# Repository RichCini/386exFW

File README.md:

# 386ex Firmware Prototyping/Design Board
386EX-target firmware design board based on the design from Ed Nisley and his Firmware Furnace column
in Circuit Cellar. The article series spanned Issues 31 to 65 (roughly 1993 to 1995). The hardware
design -- a short ISA card built on a Jameco prototyping card -- provided an easy way to interface
to the ISA bus and had memory (EEPROM/ROM/NVRAM). a timer, watchdog, LED and switch inputs, and two
types of LCD displays. 

The first part of the series (Issues 31- 46) dealt with the hardware design, while later articles
discussed something Ed called the "Firmware Furnace Task Switcher", a functional protected-mode
software platform. The software discussion began in Issue 48 and ended with Issue 65. Issue 65
seems to point to future columns on the topic, but they never seemed to appear.

## Status
The schematics have been converted and the board plotted. It has not been built yet. Of the
design elements, the only feature I didn't redraw was the bitmapped graphics LCD panel, the
discission of which began in Issue 42. Options were the Optrex (Kyocera) DMF651 640x200 or the 
Matsushita EDM-LG64AA44D 640x400 panel.

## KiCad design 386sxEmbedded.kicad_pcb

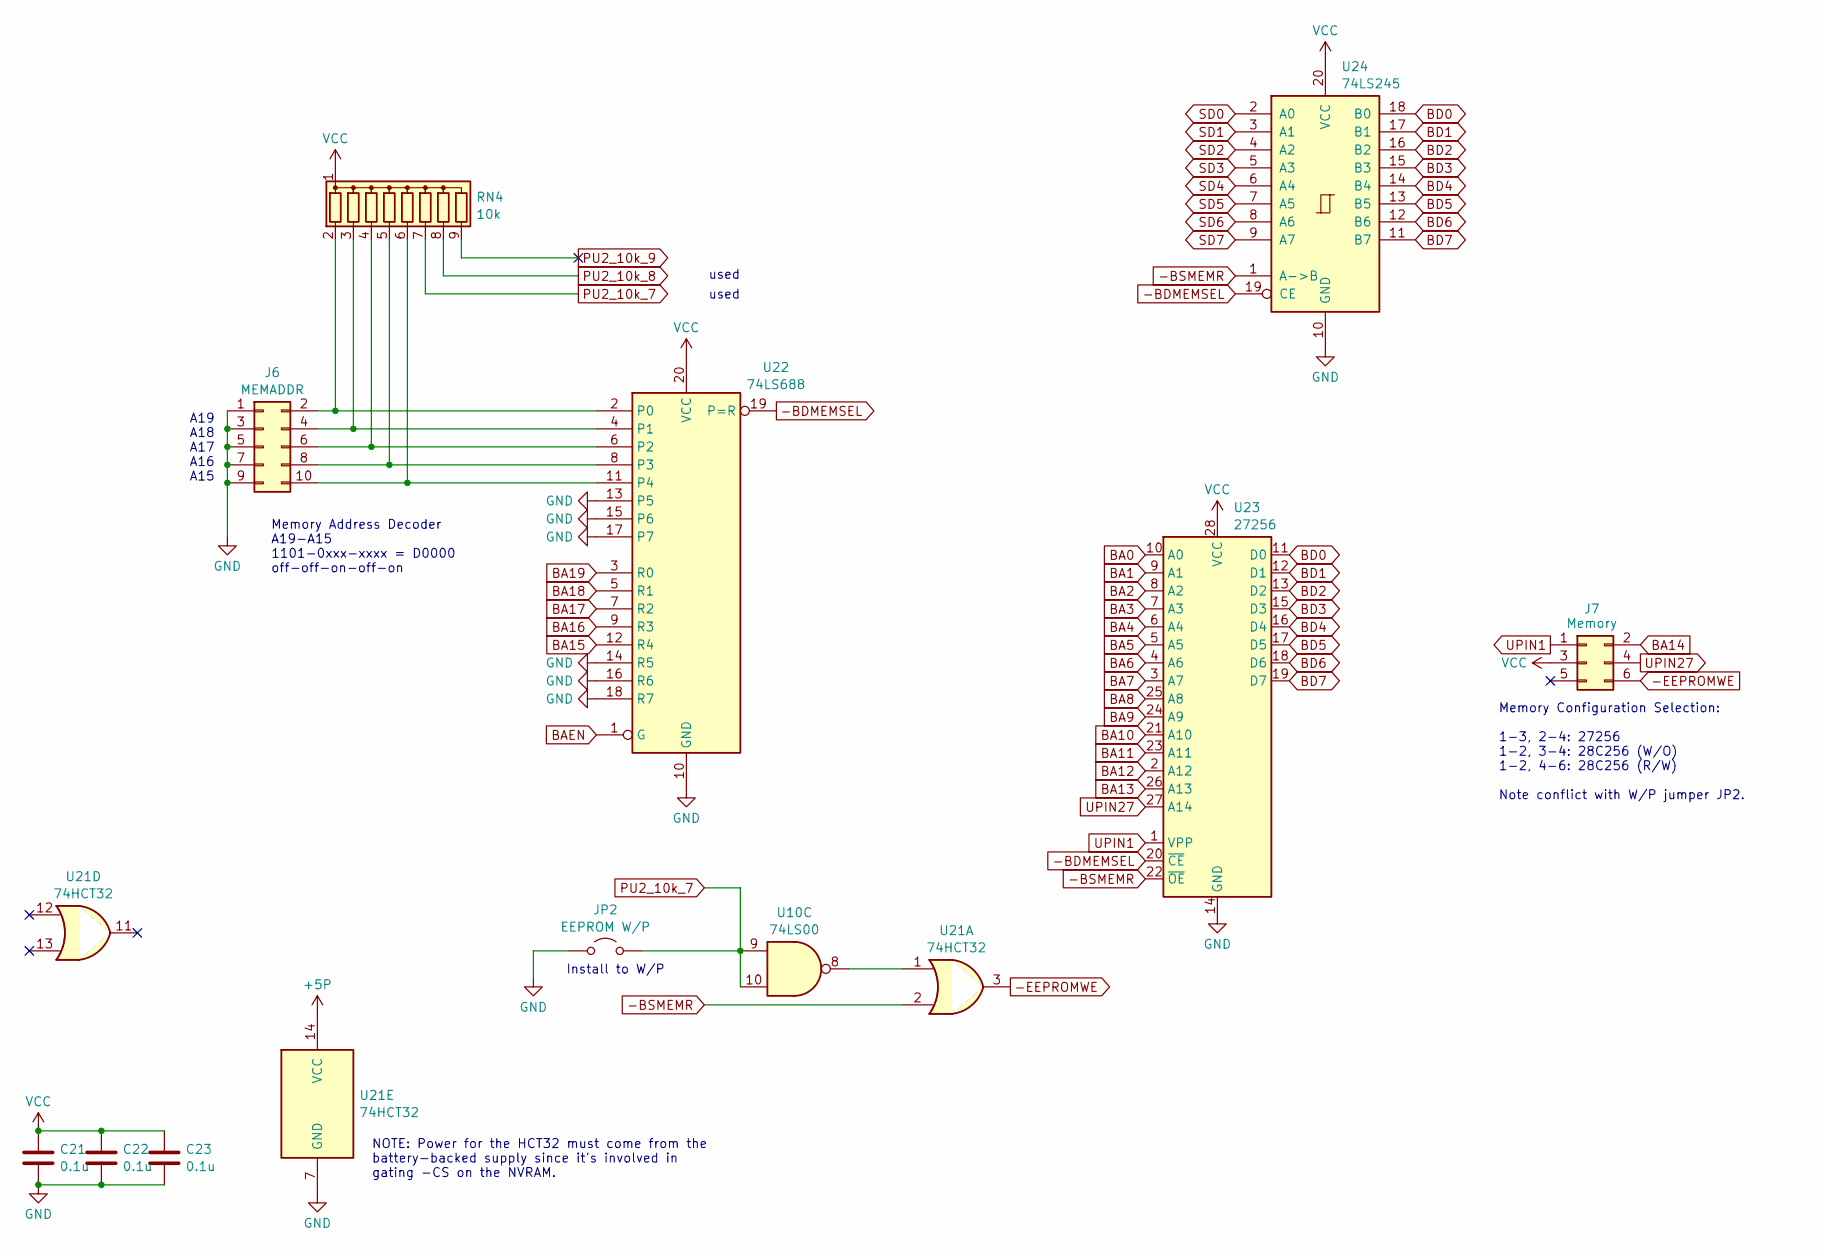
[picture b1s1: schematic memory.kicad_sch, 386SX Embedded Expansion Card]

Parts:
C21, C22, C23: 0.1u; C_Disc_D4.3mm_W1.9mm_P5.00mm
J6: MEMADDR; PinHeader_2x05_P2.54mm_Vertical
J7: Memory; PinHeader_2x03_P2.54mm_Vertical
JP2: EEPROM W/P; PinHeader_1x02_P2.54mm_Vertical
RN4: 10k; R_Array_SIP9
U10: 74LS00; DIP-14_W7.62mm_Socket
U21: 74HCT32; DIP-14_W7.62mm_Socket
U22: 74LS688; DIP-20_W7.62mm_Socket
U23: 27256; DIP-28_W15.24mm_Socket
U24: 74LS245; DIP-20_W7.62mm_Socket

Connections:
+5P: U21.14 (VCC); also elsewhere on the board
-BDMEMSEL: U22.19 (P=R), U23.20 (~CE), U24.19 (CE); also elsewhere on the board
-BSMEMR: U21.2, U23.22 (~OE), U24.1 (A->B); also elsewhere on the board
-EEPROMWE: J7.6, U21.3
BA0: U23.10 (A0); also elsewhere on the board
BA1: U23.9 (A1); also elsewhere on the board
BA2: U23.8 (A2); also elsewhere on the board
BA3: U23.7 (A3); also elsewhere on the board
BA4: U23.6 (A4); also elsewhere on the board
BA5: U23.5 (A5); also elsewhere on the board
BA6: U23.4 (A6); also elsewhere on the board
BA7: U23.3 (A7); also elsewhere on the board
BA8: U23.25 (A8); also elsewhere on the board
BA9: U23.24 (A9); also elsewhere on the board
BA10: U23.21 (A10); also elsewhere on the board
BA11: U23.23 (A11); also elsewhere on the board
BA12: U23.2 (A12); also elsewhere on the board
BA13: U23.26 (A13); also elsewhere on the board
BA14: J7.2; also elsewhere on the board
BA15: U22.12 (R4); also elsewhere on the board
BA16: U22.9 (R3); also elsewhere on the board
BA17: U22.7 (R2); also elsewhere on the board
BA18: U22.5 (R1); also elsewhere on the board
BA19: U22.3 (R0); also elsewhere on the board
BAEN: U22.1 (G); also elsewhere on the board
BD0: U23.11 (D0), U24.18 (B0); also elsewhere on the board
BD1: U23.12 (D1), U24.17 (B1); also elsewhere on the board
BD2: U23.13 (D2), U24.16 (B2); also elsewhere on the board
BD3: U23.15 (D3), U24.15 (B3); also elsewhere on the board
BD4: U23.16 (D4), U24.14 (B4); also elsewhere on the board
BD5: U23.17 (D5), U24.13 (B5); also elsewhere on the board
BD6: U23.18 (D6), U24.12 (B6); also elsewhere on the board
BD7: U23.19 (D7), U24.11 (B7); also elsewhere on the board
GND: C21.2, C22.2, C23.2, J6.1, J6.3, J6.5, J6.7, J6.9, JP2.1 (A), U21.7 (GND), U22.10 (GND), U22.13 (P5), U22.14 (R5), U22.15 (P6), U22.16 (R6), U22.17 (P7), U22.18 (R7), U23.14 (GND), U24.10 (GND); also elsewhere on the board
unnamed: J6.2, RN4.2 (R1), U22.2 (P0)
unnamed: J6.4, RN4.3 (R2), U22.4 (P1)
unnamed: J6.6, RN4.4 (R3), U22.6 (P2)
unnamed: J6.8, RN4.5 (R4), U22.8 (P3)
unnamed: J6.10, RN4.6 (R5), U22.11 (P4)
unnamed: U10.8, U21.1
PU2_10k_7: JP2.2 (B), RN4.7 (R6), U10.9, U10.10
PU2_10k_8: RN4.8 (R7); also elsewhere on the board
PU2_10k_9: RN4.9 (R8)
SD0: U24.2 (A0); also elsewhere on the board
SD1: U24.3 (A1); also elsewhere on the board
SD2: U24.4 (A2); also elsewhere on the board
SD3: U24.5 (A3); also elsewhere on the board
SD4: U24.6 (A4); also elsewhere on the board
SD5: U24.7 (A5); also elsewhere on the board
SD6: U24.8 (A6); also elsewhere on the board
SD7: U24.9 (A7); also elsewhere on the board
UPIN1: J7.1, U23.1 (VPP)
UPIN27: J7.4, U23.27 (A14)
VCC: C21.1, C22.1, C23.1, J7.3, RN4.1 (common), U22.20 (VCC), U23.28 (VCC), U24.20 (VCC); also elsewhere on the board

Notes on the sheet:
used
NOTE: Power for the HCT32 must come from the battery-backed supply since it's involved in gating -CS on the NVRAM.
Memory Address Decoder A19-A15 1101-0xxx-xxxx = D0000 off-off-on-off-on
Memory Configuration Selection: 1-3, 2-4: 27256 1-2, 3-4: 28C256 (W/O) 1-2, 4-6: 28C256 (R/W) Note conflict with W/P jumper JP2.
Install to W/P
A19 A18 A17 A16 A15

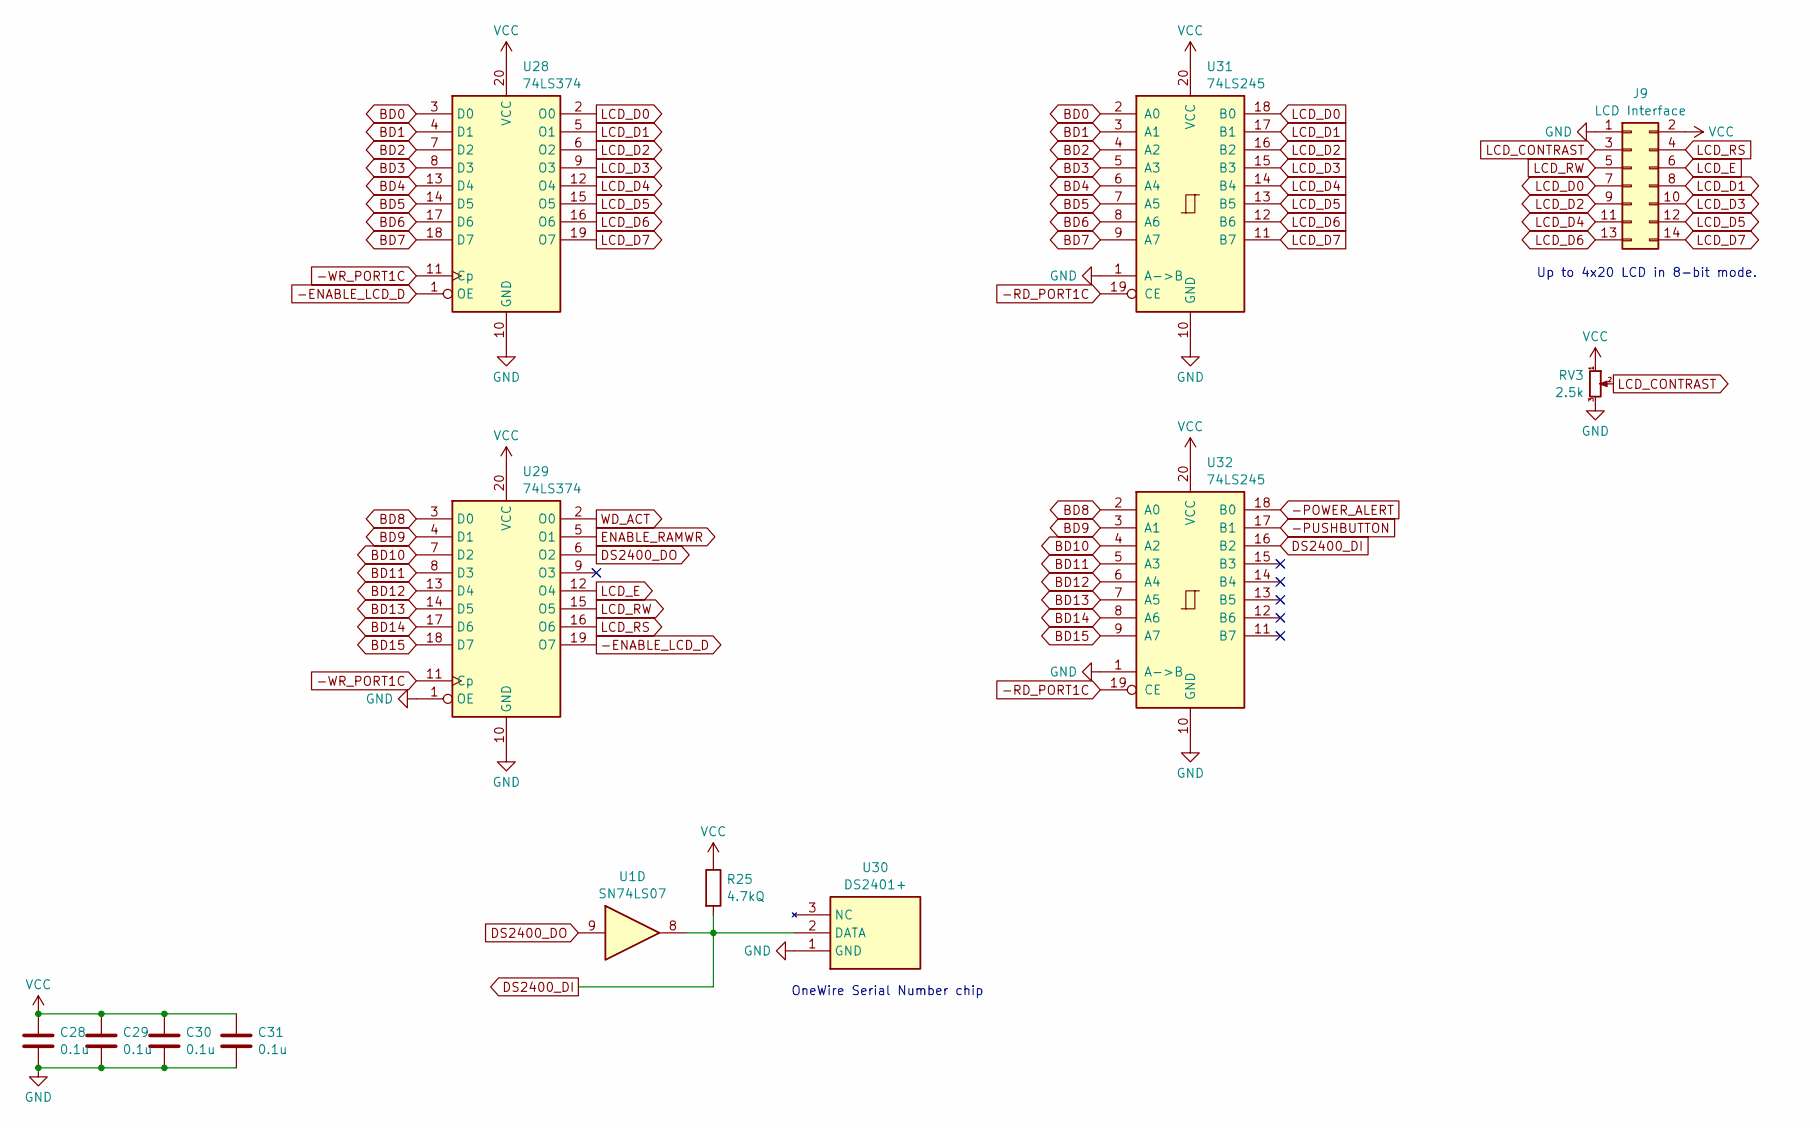
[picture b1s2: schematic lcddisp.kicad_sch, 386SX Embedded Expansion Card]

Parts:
C28, C29, C30, C31: 0.1u; C_Disc_D4.3mm_W1.9mm_P5.00mm
J9: LCD Interface; IDC-Header_2x07_P2.54mm_Vertical
R25: 4.7kQ; R_Axial_DIN0207_L6.3mm_D2.5mm_P7.62mm_Horizontal
RV3: 2.5k; Potentiometer_Bourns_3266W_Vertical
U1: SN74LS07; DIP-14_W7.62mm_Socket
U28, U29: 74LS374; DIP-20_W7.62mm_Socket
U30: DS2401+; TO-92L_Inline; Mouser Part Number 700-DS2401
U31, U32: 74LS245; DIP-20_W7.62mm_Socket

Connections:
-ENABLE_LCD_D: U28.1 (OE), U29.19 (O7)
-POWER_ALERT: U32.18 (B0); also elsewhere on the board
-PUSHBUTTON: U32.17 (B1); also elsewhere on the board
-RD_PORT1C: U31.19 (CE), U32.19 (CE); also elsewhere on the board
-WR_PORT1C: U28.11 (Cp), U29.11 (Cp); also elsewhere on the board
BD0: U28.3 (D0), U31.2 (A0); also elsewhere on the board
BD1: U28.4 (D1), U31.3 (A1); also elsewhere on the board
BD2: U28.7 (D2), U31.4 (A2); also elsewhere on the board
BD3: U28.8 (D3), U31.5 (A3); also elsewhere on the board
BD4: U28.13 (D4), U31.6 (A4); also elsewhere on the board
BD5: U28.14 (D5), U31.7 (A5); also elsewhere on the board
BD6: U28.17 (D6), U31.8 (A6); also elsewhere on the board
BD7: U28.18 (D7), U31.9 (A7); also elsewhere on the board
BD8: U29.3 (D0), U32.2 (A0); also elsewhere on the board
BD9: U29.4 (D1), U32.3 (A1); also elsewhere on the board
BD10: U29.7 (D2), U32.4 (A2); also elsewhere on the board
BD11: U29.8 (D3), U32.5 (A3); also elsewhere on the board
BD12: U29.13 (D4), U32.6 (A4); also elsewhere on the board
BD13: U29.14 (D5), U32.7 (A5); also elsewhere on the board
BD14: U29.17 (D6), U32.8 (A6); also elsewhere on the board
BD15: U29.18 (D7), U32.9 (A7); also elsewhere on the board
DS2400_DI: R25.2, U1.8, U30.2 (DATA), U32.16 (B2)
DS2400_DO: U1.9, U29.6 (O2)
ENABLE_RAMWR: U29.5 (O1); also elsewhere on the board
GND: C28.2, C29.2, C30.2, C31.2, J9.1, RV3.3, U28.10 (GND), U29.1 (OE), U29.10 (GND), U30.1 (GND), U31.1 (A->B), U31.10 (GND), U32.1 (A->B), U32.10 (GND); also elsewhere on the board
LCD_CONTRAST: J9.3, RV3.2
LCD_D0: J9.7, U28.2 (O0), U31.18 (B0)
LCD_D1: J9.8, U28.5 (O1), U31.17 (B1)
LCD_D2: J9.9, U28.6 (O2), U31.16 (B2)
LCD_D3: J9.10, U28.9 (O3), U31.15 (B3)
LCD_D4: J9.11, U28.12 (O4), U31.14 (B4)
LCD_D5: J9.12, U28.15 (O5), U31.13 (B5)
LCD_D6: J9.13, U28.16 (O6), U31.12 (B6)
LCD_D7: J9.14, U28.19 (O7), U31.11 (B7)
LCD_E: J9.6, U29.12 (O4)
LCD_RS: J9.4, U29.16 (O6)
LCD_RW: J9.5, U29.15 (O5)
VCC: C28.1, C29.1, C30.1, C31.1, J9.2, R25.1, RV3.1, U28.20 (VCC), U29.20 (VCC), U31.20 (VCC), U32.20 (VCC); also elsewhere on the board
WD_ACT: U29.2 (O0); also elsewhere on the board

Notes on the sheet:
OneWire Serial Number chip
Up to 4x20 LCD in 8-bit mode.

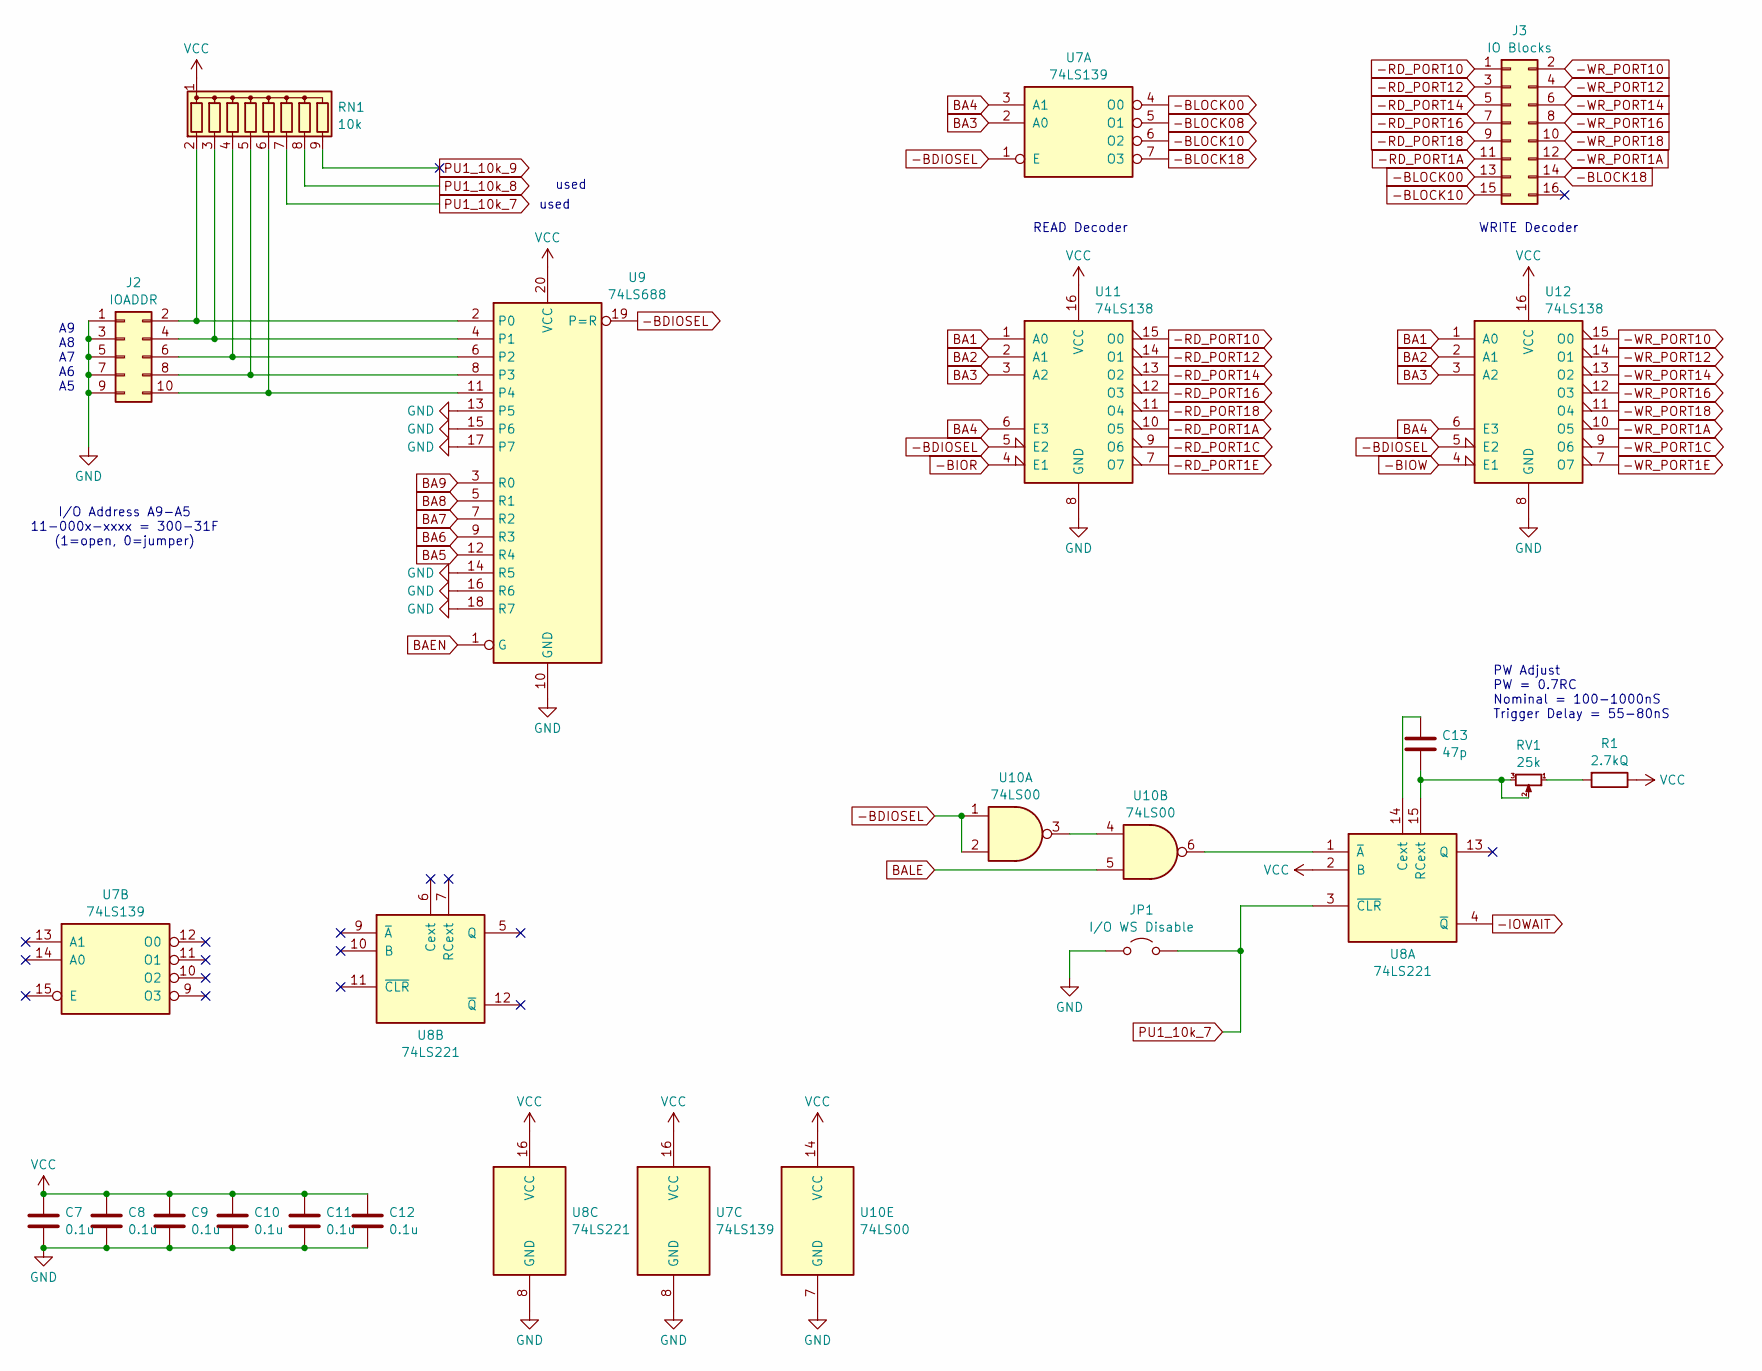
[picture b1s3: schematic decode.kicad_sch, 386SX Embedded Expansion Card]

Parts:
C7, C8, C9, C10, C11, C12: 0.1u; C_Disc_D4.3mm_W1.9mm_P5.00mm
C13: 47p; C_Disc_D3.0mm_W1.6mm_P2.50mm
J2: IOADDR; PinHeader_2x05_P2.54mm_Vertical
J3: IO Blocks; PinHeader_2x08_P2.54mm_Vertical
JP1: I/O WS Disable; PinHeader_1x02_P2.54mm_Vertical
R1: 2.7kQ; R_Axial_DIN0207_L6.3mm_D2.5mm_P7.62mm_Horizontal
RN1: 10k; R_Array_SIP9
RV1: 25k; Potentiometer_Bourns_3266W_Vertical
U7: 74LS139; DIP-16_W7.62mm_Socket
U8: 74LS221; DIP-16_W7.62mm_Socket
U9: 74LS688; DIP-20_W7.62mm_Socket
U10: 74LS00; DIP-14_W7.62mm_Socket
U11, U12: 74LS138; DIP-16_W7.62mm_Socket

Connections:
-BDIOSEL: U7.1 (E), U9.19 (P=R), U10.1, U10.2, U11.5 (E2), U12.5 (E2); also elsewhere on the board
-BIOR: U11.4 (E1); also elsewhere on the board
-BIOW: U12.4 (E1); also elsewhere on the board
-BLOCK00: J3.13, U7.4 (O0)
-BLOCK08: U7.5 (O1); also elsewhere on the board
-BLOCK10: J3.15, U7.6 (O2)
-BLOCK18: J3.14, U7.7 (O3)
-IOWAIT: U8.4 (~Q); also elsewhere on the board
-PUSHBUTTON: RN1.8 (R7); also elsewhere on the board
-RD_PORT1A: J3.11, U11.10 (O5)
-RD_PORT1C: U11.9 (O6); also elsewhere on the board
-RD_PORT1E: U11.7 (O7); also elsewhere on the board
-RD_PORT10: J3.1, U11.15 (O0)
-RD_PORT12: J3.3, U11.14 (O1)
-RD_PORT14: J3.5, U11.13 (O2)
-RD_PORT16: J3.7, U11.12 (O3)
-RD_PORT18: J3.9, U11.11 (O4)
-WR_PORT1A: J3.12, U12.10 (O5)
-WR_PORT1C: U12.9 (O6); also elsewhere on the board
-WR_PORT1E: U12.7 (O7); also elsewhere on the board
-WR_PORT10: J3.2, U12.15 (O0)
-WR_PORT12: J3.4, U12.14 (O1)
-WR_PORT14: J3.6, U12.13 (O2)
-WR_PORT16: J3.8, U12.12 (O3)
-WR_PORT18: J3.10, U12.11 (O4)
BA1: U11.1 (A0), U12.1 (A0); also elsewhere on the board
BA2: U11.2 (A1), U12.2 (A1); also elsewhere on the board
BA3: U7.2 (A0), U11.3 (A2), U12.3 (A2); also elsewhere on the board
BA4: U7.3 (A1), U11.6 (E3), U12.6 (E3); also elsewhere on the board
BA5: U9.12 (R4); also elsewhere on the board
BA6: U9.9 (R3); also elsewhere on the board
BA7: U9.7 (R2); also elsewhere on the board
BA8: U9.5 (R1); also elsewhere on the board
BA9: U9.3 (R0); also elsewhere on the board
BAEN: U9.1 (G); also elsewhere on the board
BALE: U10.5; also elsewhere on the board
GND: C7.2, C8.2, C9.2, C10.2, C11.2, C12.2, J2.1, J2.3, J2.5, J2.7, J2.9, JP1.1 (A), U7.8 (GND), U8.8 (GND), U9.10 (GND), U9.13 (P5), U9.14 (R5), U9.15 (P6), U9.16 (R6), U9.17 (P7), U9.18 (R7), U10.7 (GND), U11.8 (GND), U12.8 (GND); also elsewhere on the board
unnamed: J2.2, RN1.2 (R1), U9.2 (P0)
unnamed: J2.4, RN1.3 (R2), U9.4 (P1)
unnamed: J2.6, RN1.4 (R3), U9.6 (P2)
unnamed: J2.8, RN1.5 (R4), U9.8 (P3)
unnamed: J2.10, RN1.6 (R5), U9.11 (P4)
unnamed: R1.2, RV1.1
unnamed: C13.1, U8.14 (Cext)
unnamed: C13.2, RV1.2, RV1.3, U8.15 (RCext)
unnamed: U8.1 (~A), U10.6
unnamed: U10.3, U10.4
PU1_10k_7: JP1.2 (B), RN1.7 (R6), U8.3 (~CLR)
PU1_10k_9: RN1.9 (R8)
VCC: C7.1, C8.1, C9.1, C10.1, C11.1, C12.1, R1.1, RN1.1 (common), U7.16 (VCC), U8.2 (B), U8.16 (VCC), U9.20 (VCC), U10.14 (VCC), U11.16 (VCC), U12.16 (VCC); also elsewhere on the board

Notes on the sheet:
used
PW Adjust PW = 0.7RC Nominal = 100-1000nS Trigger Delay = 55-80nS
A9 A8 A7 A6 A5
I/O Address A9-A5 11-000x-xxxx = 300-31F (1=open, 0=jumper)
WRITE Decoder
READ Decoder

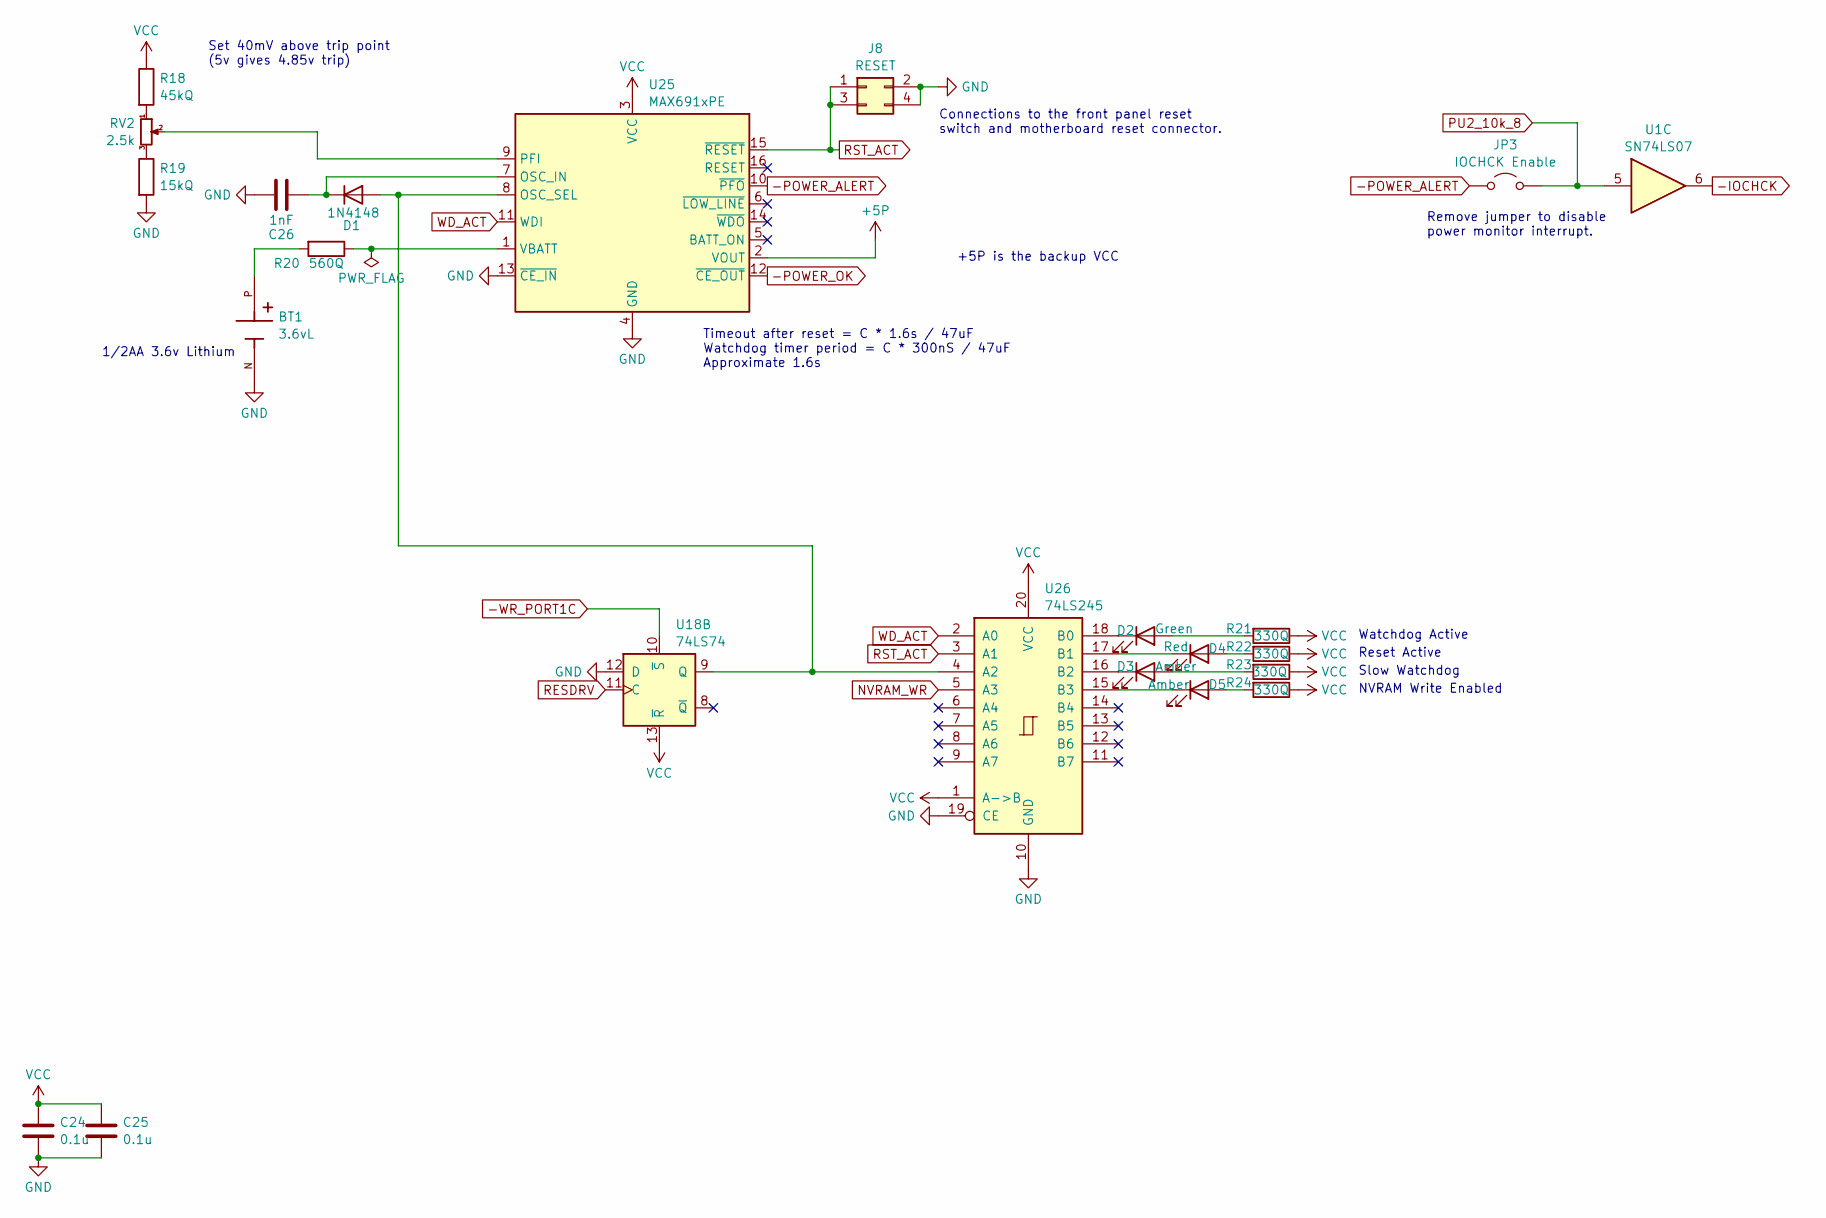
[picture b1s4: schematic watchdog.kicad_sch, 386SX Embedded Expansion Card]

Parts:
BT1: 3.6vL; BAT_2485; PARTREV B; DigiKey_Part_Number 36-2485-ND
C24, C25: 0.1u; C_Disc_D4.3mm_W1.9mm_P5.00mm
C26: 1nF; C_Disc_D3.0mm_W1.6mm_P2.50mm
D1: 1N4148; D_DO-35_SOD27_P7.62mm_Horizontal
D2: Green; LED_D3.0mm
D3, D5: Amber; LED_D3.0mm
D4: Red; LED_D3.0mm
J8: RESET; PinHeader_2x02_P2.54mm_Vertical
JP3: IOCHCK Enable; PinHeader_1x02_P2.54mm_Vertical
R18: 45kQ; R_Axial_DIN0207_L6.3mm_D2.5mm_P7.62mm_Horizontal
R19: 15kQ; R_Axial_DIN0207_L6.3mm_D2.5mm_P7.62mm_Horizontal
R20: 560Q; R_Axial_DIN0207_L6.3mm_D2.5mm_P7.62mm_Horizontal
R21, R22, R23, R24: 330Q; R_Axial_DIN0207_L6.3mm_D2.5mm_P7.62mm_Horizontal
RV2: 2.5k; Potentiometer_Bourns_3266W_Vertical
U1: SN74LS07; DIP-14_W7.62mm_Socket
U18: 74LS74; DIP-14_W7.62mm_Socket
U25: MAX691xPE; DIP-16_W7.62mm_Socket
U26: 74LS245; DIP-20_W7.62mm_Socket

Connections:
+5P: U25.2 (VOUT); also elsewhere on the board
-IOCHCK: U1.6; also elsewhere on the board
-POWER_ALERT: JP3.1 (A), U25.10 (~PFO); also elsewhere on the board
-POWER_OK: U25.12 (~CE_OUT); also elsewhere on the board
-WR_PORT1C: U18.10 (~S); also elsewhere on the board
GND: BT1.N, C24.2, C25.2, C26.2, J8.2, J8.4, R19.2, U18.12 (D), U25.4 (GND), U25.13 (~CE_IN), U26.10 (GND), U26.19 (CE); also elsewhere on the board
NVRAM_WR: U26.5 (A3); also elsewhere on the board
unnamed: BT1.P, R20.2
unnamed: D1.2 (A), U18.9 (Q), U25.8 (OSC_SEL), U26.4 (A2)
unnamed: C26.1, D1.1 (K), U25.7 (OSC_IN)
unnamed: D2.2 (A), R21.2
unnamed: D2.1 (K), U26.18 (B0)
unnamed: D3.2 (A), R23.2
unnamed: D3.1 (K), U26.16 (B2)
unnamed: D4.2 (A), R22.2
unnamed: D4.1 (K), U26.17 (B1)
unnamed: D5.2 (A), R24.2
unnamed: D5.1 (K), U26.15 (B3)
unnamed: R18.2, RV2.1
unnamed: R19.1, RV2.3
unnamed: RV2.2, U25.9 (PFI)
unnamed: R20.1, U25.1 (VBATT)
PU2_10k_8: JP3.2 (B), U1.5; also elsewhere on the board
RESDRV: U18.11 (C); also elsewhere on the board
RST_ACT: J8.1, J8.3, U25.15 (~RESET), U26.3 (A1)
VCC: C24.1, C25.1, R18.1, R21.1, R22.1, R23.1, R24.1, U18.13 (~R), U25.3 (VCC), U26.1 (A->B), U26.20 (VCC); also elsewhere on the board
WD_ACT: U25.11 (WDI), U26.2 (A0); also elsewhere on the board

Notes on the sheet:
Reset Active
Remove jumper to disable power monitor interrupt.
Slow Watchdog
Watchdog Active
+5P is the backup VCC
Set 40mV above trip point (5v gives 4.85v trip)
Timeout after reset = C * 1.6s / 47uF Watchdog timer period = C * 300nS / 47uF Approximate 1.6s
1/2AA 3.6v Lithium
Connections to the front panel reset switch and motherboard reset connector.
NVRAM Write Enabled

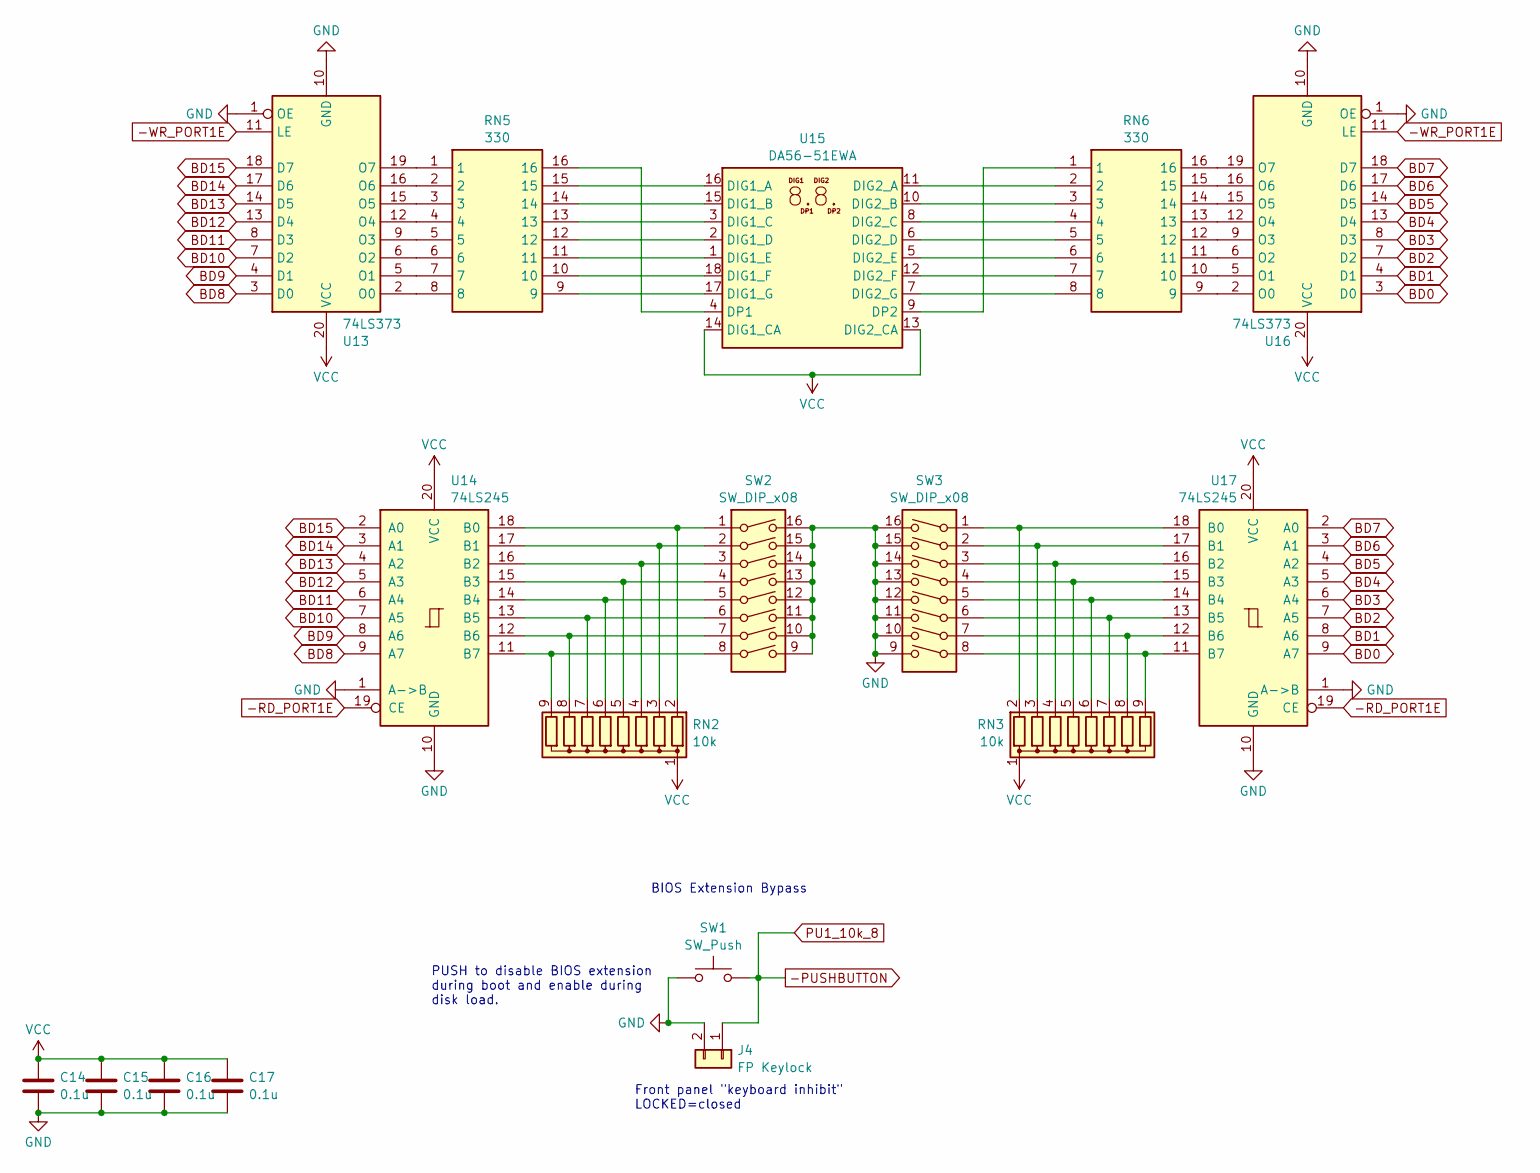
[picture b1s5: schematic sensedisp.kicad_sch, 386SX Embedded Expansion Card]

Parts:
C14, C15, C16, C17: 0.1u; C_Disc_D4.3mm_W1.9mm_P5.00mm
J4: FP Keylock; PinHeader_1x02_P2.54mm_Vertical
RN2, RN3: 10k; R_Array_SIP9
RN5, RN6: 330; DIP-16_W7.62mm_Socket; Mouser Part Number 652-4116R-1LF-330
SW1: SW_Push; SW_PUSH_6mm
SW2, SW3: SW_DIP_x08; DIP-16_W7.62mm_Socket
U13, U16: 74LS373; DIP-20_W7.62mm_Socket
U14, U17: 74LS245; DIP-20_W7.62mm_Socket
U15: DA56-51EWA; DA56-11SURKWA

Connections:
-PUSHBUTTON: J4.1, SW1.2; also elsewhere on the board
-RD_PORT1E: U14.19 (CE), U17.19 (CE); also elsewhere on the board
-WR_PORT1E: U13.11 (LE), U16.11 (LE); also elsewhere on the board
BD0: U16.3 (D0), U17.9 (A7); also elsewhere on the board
BD1: U16.4 (D1), U17.8 (A6); also elsewhere on the board
BD2: U16.7 (D2), U17.7 (A5); also elsewhere on the board
BD3: U16.8 (D3), U17.6 (A4); also elsewhere on the board
BD4: U16.13 (D4), U17.5 (A3); also elsewhere on the board
BD5: U16.14 (D5), U17.4 (A2); also elsewhere on the board
BD6: U16.17 (D6), U17.3 (A1); also elsewhere on the board
BD7: U16.18 (D7), U17.2 (A0); also elsewhere on the board
BD8: U13.3 (D0), U14.9 (A7); also elsewhere on the board
BD9: U13.4 (D1), U14.8 (A6); also elsewhere on the board
BD10: U13.7 (D2), U14.7 (A5); also elsewhere on the board
BD11: U13.8 (D3), U14.6 (A4); also elsewhere on the board
BD12: U13.13 (D4), U14.5 (A3); also elsewhere on the board
BD13: U13.14 (D5), U14.4 (A2); also elsewhere on the board
BD14: U13.17 (D6), U14.3 (A1); also elsewhere on the board
BD15: U13.18 (D7), U14.2 (A0); also elsewhere on the board
GND: C14.2, C15.2, C16.2, C17.2, J4.2, SW1.1, SW2.9, SW2.10, SW2.11, SW2.12, SW2.13, SW2.14, SW2.15, SW2.16, SW3.9, SW3.10, SW3.11, SW3.12, SW3.13, SW3.14, SW3.15, SW3.16, U13.1 (OE), U13.10 (GND), U14.1 (A->B), U14.10 (GND), U16.1 (OE), U16.10 (GND), U17.1 (A->B), U17.10 (GND); also elsewhere on the board
unnamed: RN2.2 (R1), SW2.1, U14.18 (B0)
unnamed: RN2.3 (R2), SW2.2, U14.17 (B1)
unnamed: RN2.4 (R3), SW2.3, U14.16 (B2)
unnamed: RN2.5 (R4), SW2.4, U14.15 (B3)
unnamed: RN2.6 (R5), SW2.5, U14.14 (B4)
unnamed: RN2.7 (R6), SW2.6, U14.13 (B5)
unnamed: RN2.8 (R7), SW2.7, U14.12 (B6)
unnamed: RN2.9 (R8), SW2.8, U14.11 (B7)
unnamed: RN3.2 (R1), SW3.1, U17.18 (B0)
unnamed: RN3.3 (R2), SW3.2, U17.17 (B1)
unnamed: RN3.4 (R3), SW3.3, U17.16 (B2)
unnamed: RN3.5 (R4), SW3.4, U17.15 (B3)
unnamed: RN3.6 (R5), SW3.5, U17.14 (B4)
unnamed: RN3.7 (R6), SW3.6, U17.13 (B5)
unnamed: RN3.8 (R7), SW3.7, U17.12 (B6)
unnamed: RN3.9 (R8), SW3.8, U17.11 (B7)
unnamed: RN5.8, U13.2 (O0)
unnamed: RN5.7, U13.5 (O1)
unnamed: RN5.6, U13.6 (O2)
unnamed: RN5.5, U13.9 (O3)
unnamed: RN5.4, U13.12 (O4)
unnamed: RN5.3, U13.15 (O5)
unnamed: RN5.2, U13.16 (O6)
unnamed: RN5.1, U13.19 (O7)
unnamed: RN5.15, U15.16 (DIG1_A)
unnamed: RN5.14, U15.15 (DIG1_B)
unnamed: RN5.13, U15.3 (DIG1_C)
unnamed: RN5.12, U15.2 (DIG1_D)
unnamed: RN5.11, U15.1 (DIG1_E)
unnamed: RN5.10, U15.18 (DIG1_F)
unnamed: RN5.9, U15.17 (DIG1_G)
unnamed: RN6.2, U15.11 (DIG2_A)
unnamed: RN6.3, U15.10 (DIG2_B)
unnamed: RN6.4, U15.8 (DIG2_C)
unnamed: RN6.5, U15.6 (DIG2_D)
unnamed: RN6.6, U15.5 (DIG2_E)
unnamed: RN6.7, U15.12 (DIG2_F)
unnamed: RN6.8, U15.7 (DIG2_G)
unnamed: RN5.16, U15.4 (DP1)
unnamed: RN6.1, U15.9 (DP2)
unnamed: RN6.9, U16.2 (O0)
unnamed: RN6.10, U16.5 (O1)
unnamed: RN6.11, U16.6 (O2)
unnamed: RN6.12, U16.9 (O3)
unnamed: RN6.13, U16.12 (O4)
unnamed: RN6.14, U16.15 (O5)
unnamed: RN6.15, U16.16 (O6)
unnamed: RN6.16, U16.19 (O7)
VCC: C14.1, C15.1, C16.1, C17.1, RN2.1 (common), RN3.1 (common), U13.20 (VCC), U14.20 (VCC), U15.13 (DIG2_CA), U15.14 (DIG1_CA), U16.20 (VCC), U17.20 (VCC); also elsewhere on the board

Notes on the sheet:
BIOS Extension Bypass
PUSH to disable BIOS extension during boot and enable during disk load.
Front panel "keyboard inhibit" LOCKED=closed

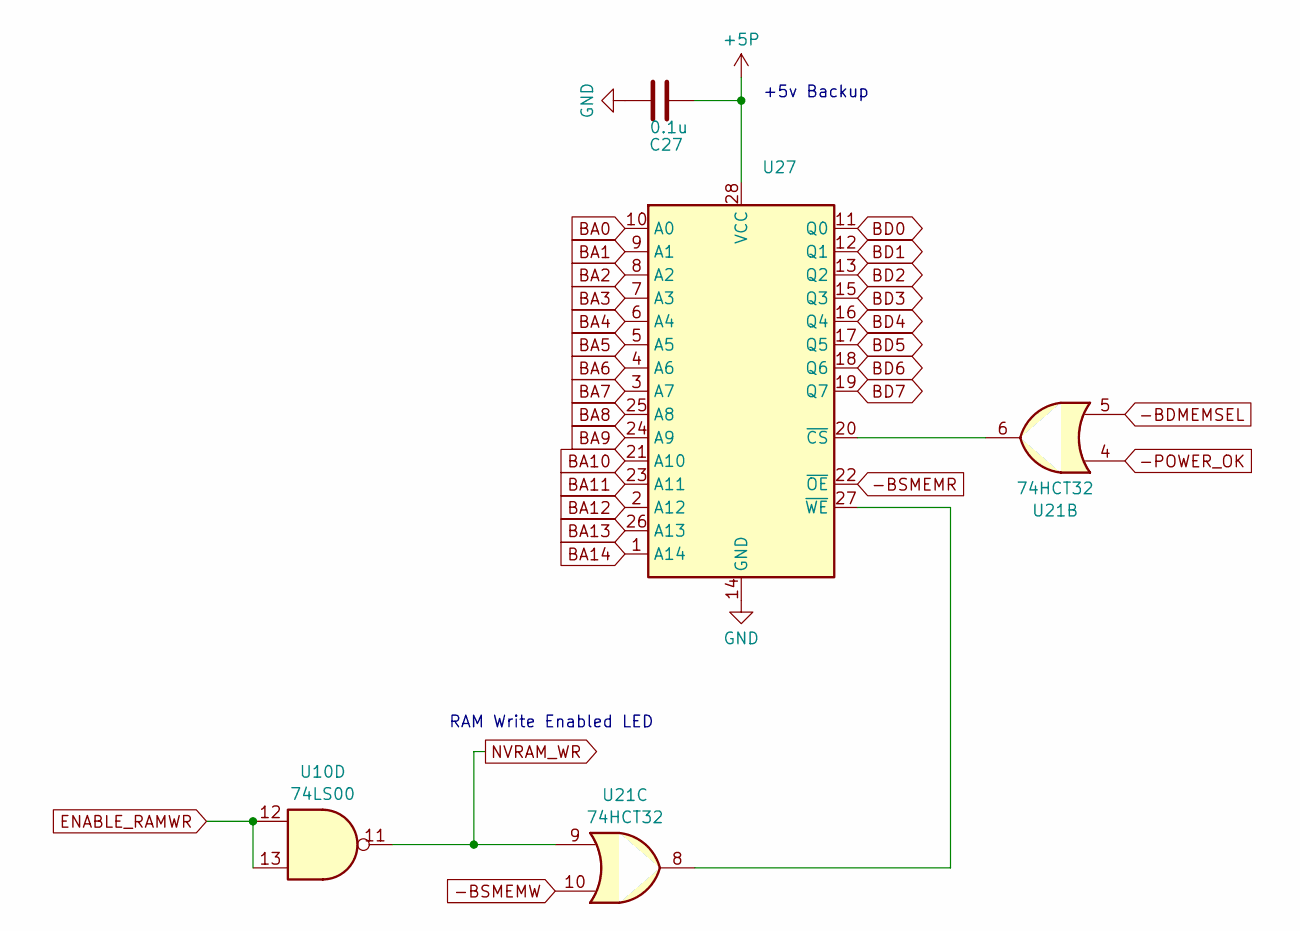
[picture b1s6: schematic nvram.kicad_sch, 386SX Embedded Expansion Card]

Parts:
C27: 0.1u; C_Disc_D4.3mm_W1.9mm_P5.00mm
U10: 74LS00; DIP-14_W7.62mm_Socket
U21: 74HCT32; DIP-14_W7.62mm_Socket
U27: HM62256BLP; DIP-28_W15.24mm_Socket

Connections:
+5P: C27.1, U27.28 (VCC); also elsewhere on the board
-BDMEMSEL: U21.5; also elsewhere on the board
-BSMEMR: U27.22 (~OE); also elsewhere on the board
-BSMEMW: U21.10; also elsewhere on the board
-POWER_OK: U21.4; also elsewhere on the board
BA0: U27.10 (A0); also elsewhere on the board
BA1: U27.9 (A1); also elsewhere on the board
BA2: U27.8 (A2); also elsewhere on the board
BA3: U27.7 (A3); also elsewhere on the board
BA4: U27.6 (A4); also elsewhere on the board
BA5: U27.5 (A5); also elsewhere on the board
BA6: U27.4 (A6); also elsewhere on the board
BA7: U27.3 (A7); also elsewhere on the board
BA8: U27.25 (A8); also elsewhere on the board
BA9: U27.24 (A9); also elsewhere on the board
BA10: U27.21 (A10); also elsewhere on the board
BA11: U27.23 (A11); also elsewhere on the board
BA12: U27.2 (A12); also elsewhere on the board
BA13: U27.26 (A13); also elsewhere on the board
BA14: U27.1 (A14); also elsewhere on the board
BD0: U27.11 (Q0); also elsewhere on the board
BD1: U27.12 (Q1); also elsewhere on the board
BD2: U27.13 (Q2); also elsewhere on the board
BD3: U27.15 (Q3); also elsewhere on the board
BD4: U27.16 (Q4); also elsewhere on the board
BD5: U27.17 (Q5); also elsewhere on the board
BD6: U27.18 (Q6); also elsewhere on the board
BD7: U27.19 (Q7); also elsewhere on the board
ENABLE_RAMWR: U10.12, U10.13; also elsewhere on the board
GND: C27.2, U27.14 (GND); also elsewhere on the board
NVRAM_WR: U10.11, U21.9; also elsewhere on the board
unnamed: U21.6, U27.20 (~CS)
unnamed: U21.8, U27.27 (~WE)

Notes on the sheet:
+5v Backup
RAM Write Enabled LED

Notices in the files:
386sxEmbedded.kicad_pcb:
Copyright (C) 1993-1995, Ed Nisley
